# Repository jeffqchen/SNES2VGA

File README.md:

# SNES2VGA

SNES2VGA Dongle for Nintendo Consoles

## Introduction

This dongle takes the AV Multi output used on various Nintendo consoles and adapts them into HD15 (VGA), so you can use the commonly available VGA cable for transmitting RGBs video and stereo audio.

Note that consoles usually require RGB mods in order to output RGBs signal.

### Console Compatibility

#### Nintendo Entertainment System / Nintendo Famicom

The NES/Famicom do not generate or output RGB signals natively. They generate composite video and output it as-is or encode it to RF.

For them to output RGB, modding it with an [NESRGB](https://etim.net.au/nesrgb/) and the [Nintendo AV Multi style port](https://www.laserbear.net/products/nes-front-loader-snap-fit-multiout) is required.

*(If you installed an 8 or 9-pin MiniDin port, please check my [8DIN2VGA](https://github.com/jeffqchen/8DIN2VGA) and [9DIN2VGA](https://github.com/jeffqchen/9DIN2VGA) projects instead.)*

---------

#### Super NES / Super Famicom (Jr.)

- NTSC consoles not output RGB signals natively, and need to be modded to restore RGB output with [SNES RGB Bypass](https://github.com/borti4938/SNES_RGB_Bypass).
- PAL consoles output an RGB signal, but outputs 12V on the same pin where CSync is output on a NTSC console. Care must be taken when assembling the dongle.

---------

#### Nintendo 64

No native RGB output. Different models require different levels of modding to restore RGB output ([Simple RGB Bypass](https://voultar.com/index.php?route=product/product&product_id=50), [N64RGB](https://etim.net.au/n64rgb/), etc)

---------

#### GameCube

- NTSC consoles don't output RGB signals. RGB modding, such as [GCVideo](https://github.com/ikorb/gcvideo), is required.
- PAL consoles support RGB output natively, however the same `12V on CSync ordeal` is still present.

## Sync

You can choose among CSync, Luma and composite video as your sync signal with the jumper on the PCB.

**WARNING**: PAL consoles output 12V on the CSync pin. CSync related components should NOT be populated if you are building this dongle for a PAL console.

## Audio

Audio can be sent within the VGA cable, or broken out from the 3.5mm jack on the dongle. Buzzing may be noticeable when audio is transmitted through the VGA cable in certain scenes in certain games. This is due to insufficient shielding in most VGA cables. If you find the buzzing to be annoying, please use the 3.5mm jack on the dongle for audio outputting. This will ensure the cleanest audio output.

------

## Variation - [N64D2VGA](./N64D2VGA)

This one works with my [N64Digital mini HDMI to Full HDMI Dongle](../../../N64Digital-Mini-To-Full-HDMI-Adapter) so you could achieve analogue RGBS & digital dual output with full sized plugs without interference.

-----

## Parts

### Common Parts

- PCB
  - [Main](https://oshpark.com/projects/JstxPxyZ)
  - [Sub](https://oshpark.com/shared_projects/RpSdS3qo)

- Nintendo AV Plug - [Link](https://github.com/jeffqchen/JeffParts/blob/main/Connectors/Nintendo%20AV%20Plug/info.md)

- VGA Port Slim, Female - [Link](https://github.com/jeffqchen/JeffParts/blob/main/Connectors/HD15/Slim/Female%20PCB/info.md)

- Vertical 3.5mm Headphone Jack - [Link](https://github.com/jeffqchen/JeffParts/blob/main/Connectors/3.5mm%20Audio%20Jack/Vertical%205-Pin%20PCB/info.md)

- [1x] M3x20mm screw and nut - [Link](https://github.com/jeffqchen/JeffParts/blob/main/Parts/M2%20M3%20Hex%20Screw%20%26%20Nut/info.md)

- [2x] Imperials 0603 SMD Capacitor 6.3V 10uF - C4, C5

- 3D Printed Shell
  - [Top](https://github.com/jeffqchen/SNES2VGA/blob/main/3D%20Print/SNES2VGA/Top.stl)
  - [Bottom](https://github.com/jeffqchen/SNES2VGA/blob/main/3D%20Print/SNES2VGA/Bottom.stl)

---

### NTSC Configuration

- C1, C2, C3: [3x] 220uF / 6.3V / Imperial 1206 Size - [Link](https://github.com/jeffqchen/JeffParts/blob/main/Components/220uF%20SMD%20Cap/info.md)
- [1x] Imperial SMD 0603 Resistor 470 Ohm - R1, **ONLY** if you choose CSync

---

### PAL Configuration

- C6: [1x] 220uF / 6.3V / Imperial 1206 Size - [Link](https://github.com/jeffqchen/JeffParts/blob/main/Components/220uF%20SMD%20Cap/info.md)
- [4x] Imperial SMD 0603 Resistor 75 Ohm - R2, R3, R4, R5

---

## Printing the Shell

Print the files with the split face facing downwards.

Print with support.

For a better mating surface finishing, use raft for bed adhesion.

---

## PCB Assembly

### Solder sub PCB to the main

First, align the sub PCB on top of the main PCB, align with the helper line and make sure the correct sides are facing the outside. Solder the two outside-most castellated pins and pads one by one, making sure the outside of the two boards are flush, so the plug can be soldered properly. Then proceed to solder the rest of the castellated pins to the pads.

### Solder on the video plug

Next, take a Nintendo video plug. Note the pins on the soldering side are sticking out straight. Now **bend** both rows of the pins inwards, with the help of the edge of a table. This way, the pins will actually be able to touch the pads on the PCB compound.

Tuck the plug onto the compound PCB. Make sure the plug is pointing the correct way up - the notched side of the plug is up, and the side with the smaller sub PCB is up. Align the pins to the pads as good as possible. Make sure there is no gap between the plug and the PCB on the mating edge. Then, solder one pin on each side with a generous amount of solder. Remelt and adjust the position if needed. Then proceed and solder the rest of the pins to the PCB with generous amount of solder.

### SMD Components

Solder on the SMD components. Note for NTSC and PAL consoles, the component configurations are **quite different**. Please follow the instructions on the silk screen.

---

### NTSC Configuration

- Populate C1, C2, C3

#### Choose A Sync

##### CSync
- Populate R1
- Leave JP2 open

##### Composite (CVBS) or Luma As Sync
- Do NOT populate R1
- Short one side of jumper JP1 for CVBS or Luma. Choose only **ONE**
- Short JP2

---

### PAL Configuration

- **DO NOT** populate R1
- Populate R2, R3, R4, R5
- Short C1, C2, C3 with individual conductors
- Populate C6

#### Choose A Sync between Composite (CVBS) or Luma

- Short one side of jumper JP1 for CVBS (recommended) or Luma. Choose only **ONE**
- Leave JP2 open

---

### Through hole components

Solder on the through hole VGA and 3.5mm audio port. Note they are supposed to be on the bottom side of the PCB. Pay attention to the silk screen markings.

---

## Final Assembly

Tuck the assembled PCB into one side of the shell. Make sure the video plug fits correctly in. Then drop the other side of the shell in and slowly bring the two sides to a close. Inspect the shells for any remaining support material if you can't correctly close it up. Finally, put in the screw and nut to secure the whole assembly.

---
## Misc Info
Non-CSync signals are incompatible with the AV3 input on the OSSC. Only TTL CSync works with AV3 on the OSSC.

---

## Special Thanks

Mike Chi - Beloved creator of RetroTink
- https://www.retrotink.com

Javier Rodas
- https://twitter.com/JaviRodasG

---

Shield: [![CC BY-SA 4.0][cc-by-sa-shield]][cc-by-sa]

This work is licensed under a
[Creative Commons Attribution-ShareAlike 4.0 International License][cc-by-sa].

[![CC BY-SA 4.0][cc-by-sa-image]][cc-by-sa]

[cc-by-sa]: http://creativecommons.org/licenses/by-sa/4.0/
[cc-by-sa-image]: https://licensebuttons.net/l/by-sa/4.0/88x31.png
[cc-by-sa-shield]: https://img.shields.io/badge/License-CC%20BY--SA%204.0-lightgrey.svg

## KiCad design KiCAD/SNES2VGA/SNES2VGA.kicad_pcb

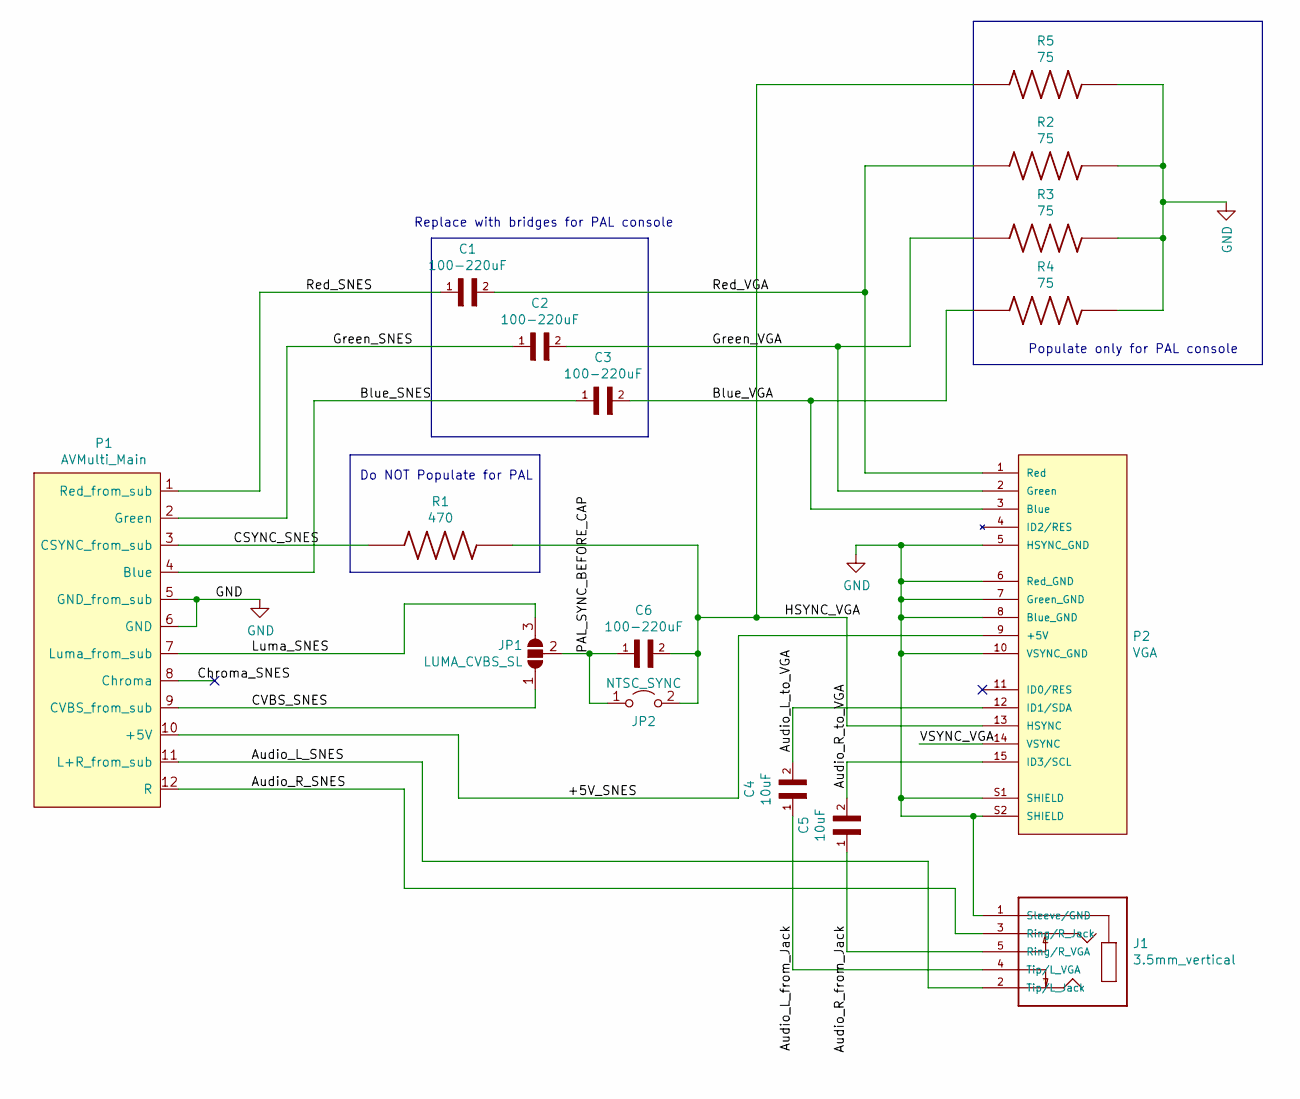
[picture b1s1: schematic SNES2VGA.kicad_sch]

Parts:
C1, C2, C3, C6: 100-220uF; Cap_SMD_1206
C4, C5: 10uF; Cap_SMD_0603
J1: 3.5mm_vertical; PARTREV 1.01
JP1: LUMA_CVBS_SL; SolderJumper-3_P1.3mm_Open_RoundedPad1.0x1.5mm
JP2: NTSC_SYNC; SolderJumper-2_P1.3mm_Open_RoundedPad1.0x1.5mm
P1: AVMulti_Main; AV_Multi_Main
P2: VGA; VGA_female_rightangle_slim; PARTREV N/A
R1: 470; Resistor_SMD_0603
R2, R3, R4, R5: 75; Resistor_SMD_0603

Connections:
/+5V_SNES: P1.10 (+5V), P2.9 (+5V)
/Audio_L_SNES: J1.2 (Tip/L_Jack), P1.11 (L+R_from_sub)
/Audio_L_from_Jack: C4.1, J1.4 (Tip/L_VGA)
/Audio_L_to_VGA: C4.2, P2.12 (ID1/SDA)
/Audio_R_SNES: J1.3 (Ring/R_Jack), P1.12 (R)
/Audio_R_from_Jack: C5.1, J1.5 (Ring/R_VGA)
/Audio_R_to_VGA: C5.2, P2.15 (ID3/SCL)
/Blue_SNES: C3.1, P1.4 (Blue)
/Blue_VGA: C3.2, P2.3 (Blue), R4.1
/CSYNC_SNES: P1.3 (CSYNC_from_sub), R1.1
/CVBS_SNES: JP1.1 (A), P1.9 (CVBS_from_sub)
/Chroma_SNES: P1.8 (Chroma)
/Green_SNES: C2.1, P1.2 (Green)
/Green_VGA: C2.2, P2.2 (Green), R3.1
/HSYNC_VGA: C6.2, JP2.2 (B), P2.13 (HSYNC), R1.2, R5.1
/Luma_SNES: JP1.3 (B), P1.7 (Luma_from_sub)
/PAL_SYNC_BEFORE_CAP: C6.1, JP1.2 (C), JP2.1 (A)
/Red_SNES: C1.1, P1.1 (Red_from_sub)
/Red_VGA: C1.2, P2.1 (Red), R2.1
/VSYNC_VGA: P2.14 (VSYNC)
GND: J1.1 (Sleeve/GND), P1.5 (GND_from_sub), P1.6 (GND), P2.5 (HSYNC_GND), P2.6 (Red_GND), P2.7 (Green_GND), P2.8 (Blue_GND), P2.10 (VSYNC_GND), P2.S1 (SHIELD), P2.S2 (SHIELD), R2.2, R3.2, R4.2, R5.2

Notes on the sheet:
Do NOT Populate for PAL
Replace with bridges for PAL console
Populate only for PAL console

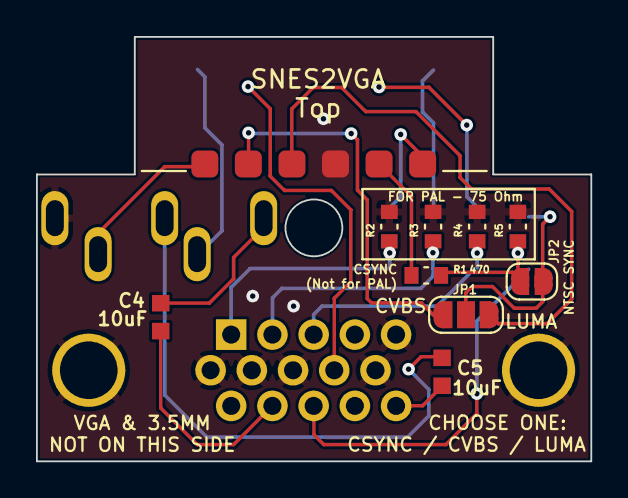
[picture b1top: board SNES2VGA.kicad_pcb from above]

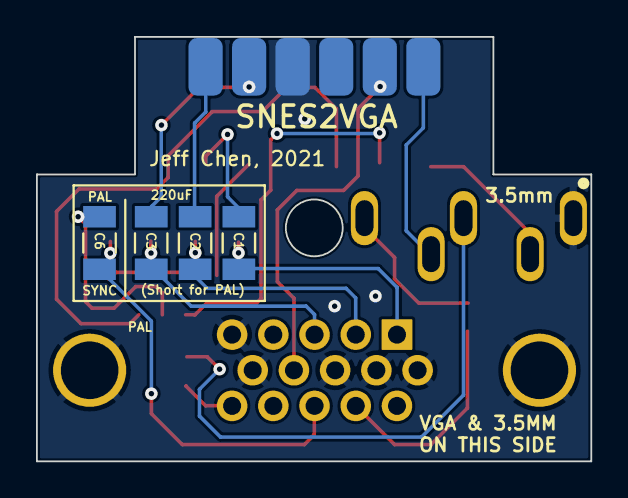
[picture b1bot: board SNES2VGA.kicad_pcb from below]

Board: 2 copper layers, 30.8 x 23.6 mm, 16 parts (6 on the bottom side), 19 nets.

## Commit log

2021-09-18 Initial upload
2021-09-18 Add Image
2021-10-04 Add N64D2VGA Files
2021-10-04 Rearrange 3D print files
2021-10-24 Update PCB
2021-12-31 Update N64D2VGA Page
2021-12-31 Update main readme
2021-12-31 Add 3D Print Files
2022-03-23 Update 3.5mm URL
2022-03-23 Update VGA URL
2022-08-09 Change license type
2023-01-30 KiCAD Project Revision
2025-07-25 added single note for gamecubes
2025-07-25 Update README.md
    Rewrite console support section to contain detailed and proper information.
2026-06-11 Fix jumper references in README
    Updated jumper references from J1/J2 to JP1/JP2 in README.
2026-06-11 Update jumper instructions for CVBS configuration
2026-06-11 Update README with sync configuration details
